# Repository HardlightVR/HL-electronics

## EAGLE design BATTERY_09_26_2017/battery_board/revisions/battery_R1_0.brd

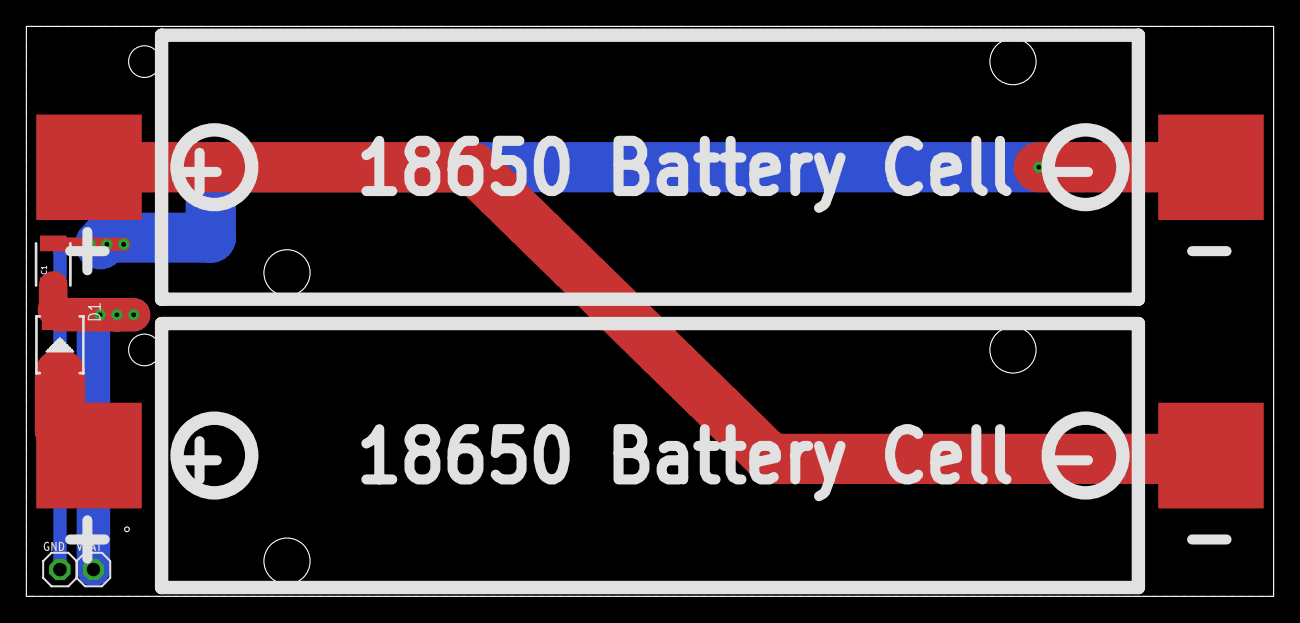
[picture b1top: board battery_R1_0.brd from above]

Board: 2 copper layers, 94.5 x 43.2 mm, 6 parts (0 on the bottom side), 4 nets.

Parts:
C1: 47uF; 1210
CELL1, CELL2: KSE-1042P
D1: 28V-5A; DO-214AA
GND: WPAD-1-PTH-2.54
VBAT: WPAD-1-PTH-2.54

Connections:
7V2: CELL2.+, D1.+
CELL1: CELL1.+, CELL2.-
GND: C1.2, CELL1.-, GND.1
VBAT: C1.1, D1.-, VBAT.1

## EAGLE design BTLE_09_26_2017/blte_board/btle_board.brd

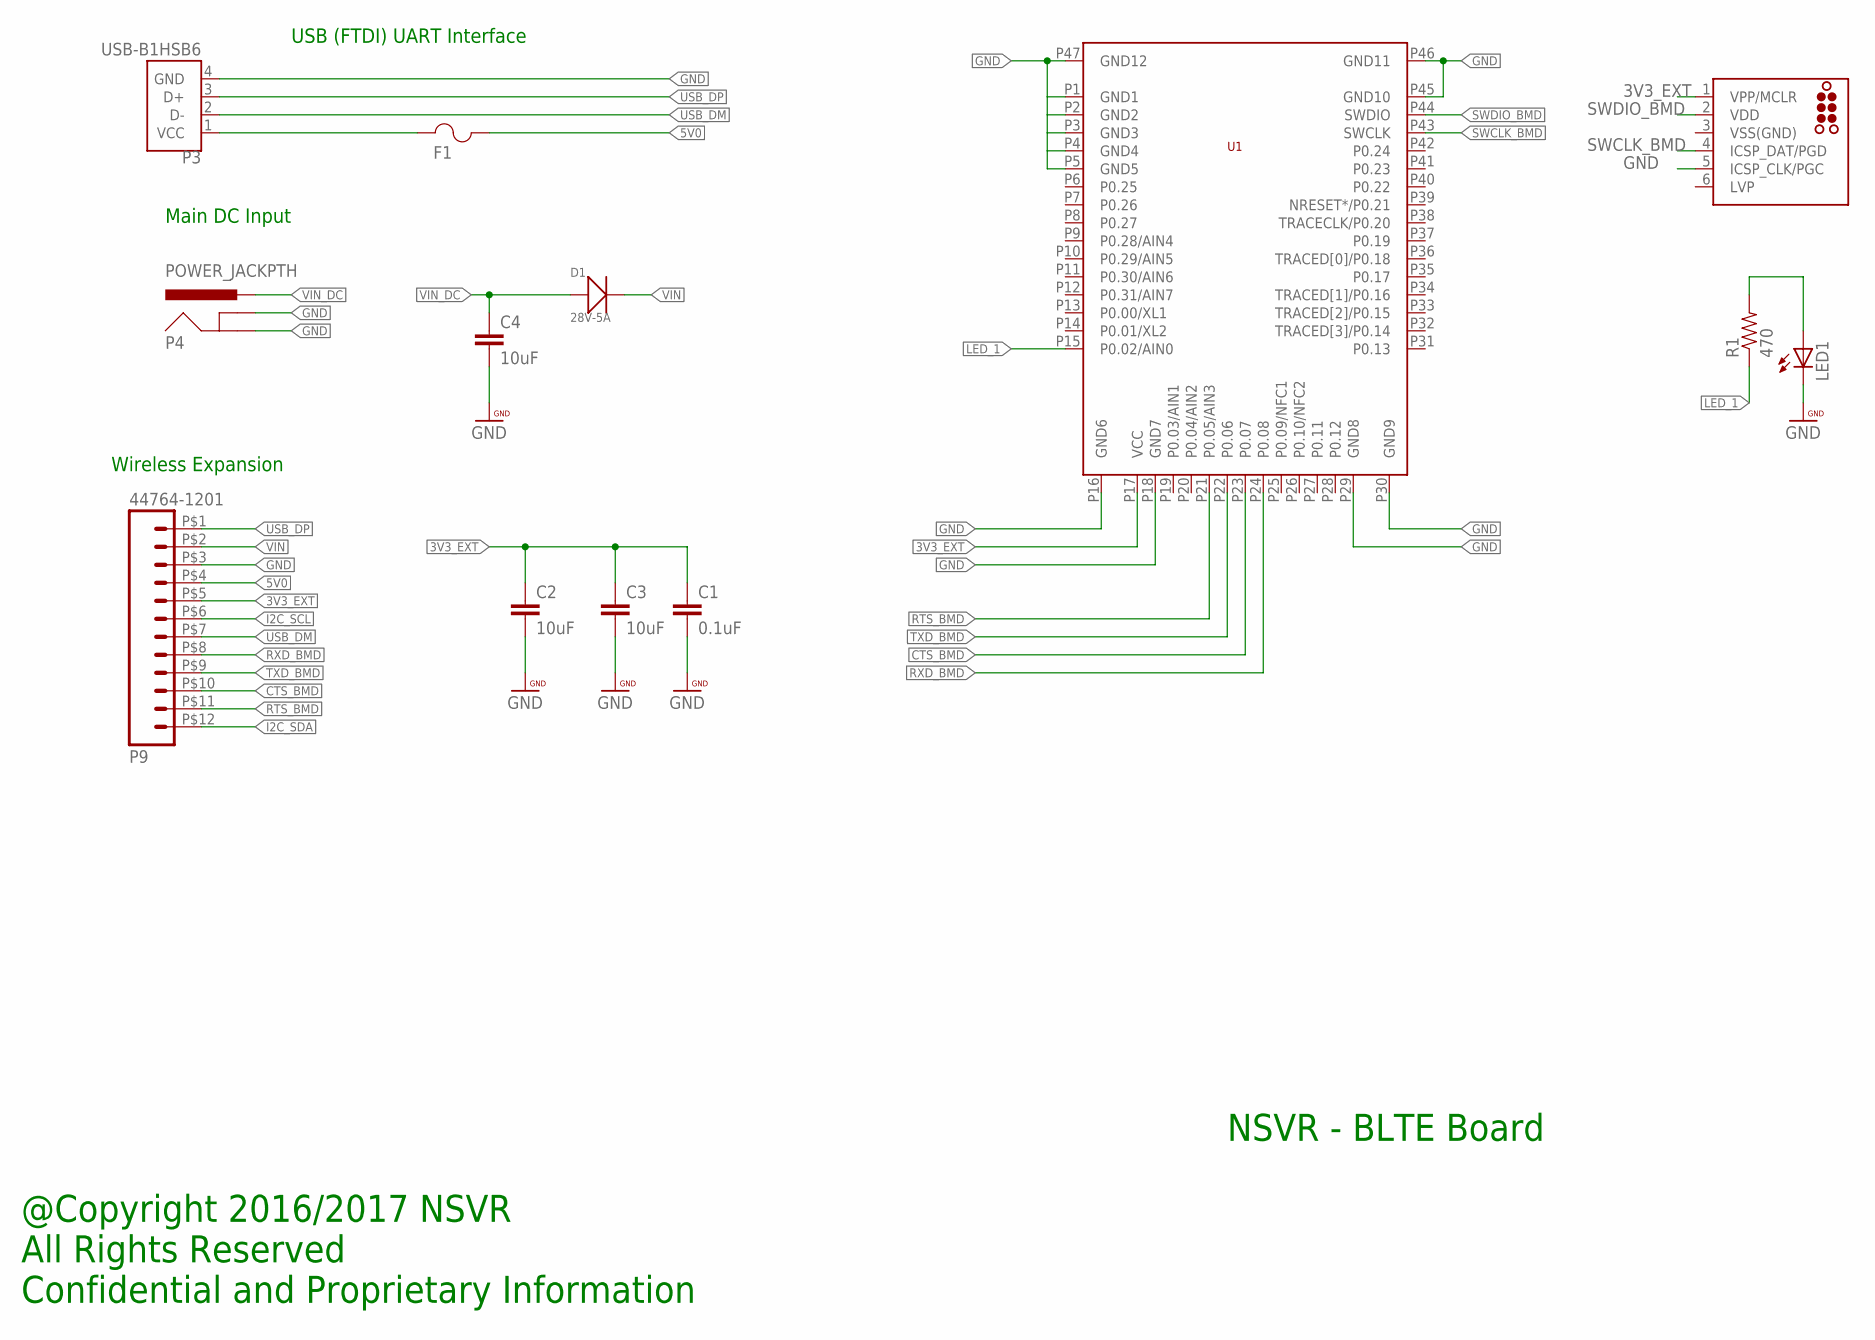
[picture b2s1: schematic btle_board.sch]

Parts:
C1: 0.1uF; 0603-CAP
C2, C3, C4: 10uF; 0603-CAP
D1: 28V-5A; DO-214AA
F1: 1206L050YR; 1206LSERIES
LED1: LEDCHIP-LED0603; CHIP-LED0603
P1: TC2030-MCP-NL
P3: USB-B1HSB6; OST_USB-B1HSB6
P4: POWER_JACKPTH; POWER_JACK_PTH
P9: 44764-1201
R1: 470; EIA-0402
U1: BMD-300

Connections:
3V3_EXT: C1.1, C2.1, C3.1, P1.1 (VPP/MCLR), P9.P$5 (5), U1.P17 (VCC)
5V0: F1.2, P9.P$4 (4)
CTS_BMD: P9.P$10 (10), U1.P23 (P0.07)
GND: C1.2, C2.2, C3.2, C4.2, LED1.C, P1.5 (ICSP_CLK/PGC), P3.4 (GND), P4.GND, P4.GNDBREAK, P9.P$3 (3), U1.P1 (GND1), U1.P2 (GND2), U1.P3 (GND3), U1.P4 (GND4), U1.P5 (GND5), U1.P16 (GND6), U1.P18 (GND7), U1.P29 (GND8), U1.P30 (GND9), U1.P45 (GND10), U1.P46 (GND11), U1.P47 (GND12)
I2C_SCL: P9.P$6 (6)
I2C_SDA: P9.P$12 (12)
LED1: LED1.A, R1.2
LED_1: R1.1, U1.P15 (P0.02/AIN0)
RTS_BMD: P9.P$11 (11), U1.P21 (P0.05/AIN3)
RXD_BMD: P9.P$8 (8), U1.P24 (P0.08)
SWCLK_BMD: P1.4 (ICSP_DAT/PGD), U1.P43 (SWCLK)
SWDIO_BMD: P1.2 (VDD), U1.P44 (SWDIO)
TXD_BMD: P9.P$9 (9), U1.P22 (P0.06)
USB_DM: P3.2 (D-), P9.P$7 (7)
USB_DP: P3.3 (D+), P9.P$1 (1)
VBUS_IN: F1.1, P3.1 (VCC)
VIN: D1.-, P9.P$2 (2)
VIN_DC: C4.1, D1.+, P4.PWR
VSS(GND): P1.3 (VSS(GND))

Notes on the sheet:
Wireless Expansion
Main DC Input
USB (FTDI) UART Interface
@Copyright 2016/2017 NSVR All Rights Reserved Confidential and Proprietary Information
NSVR - BLTE Board

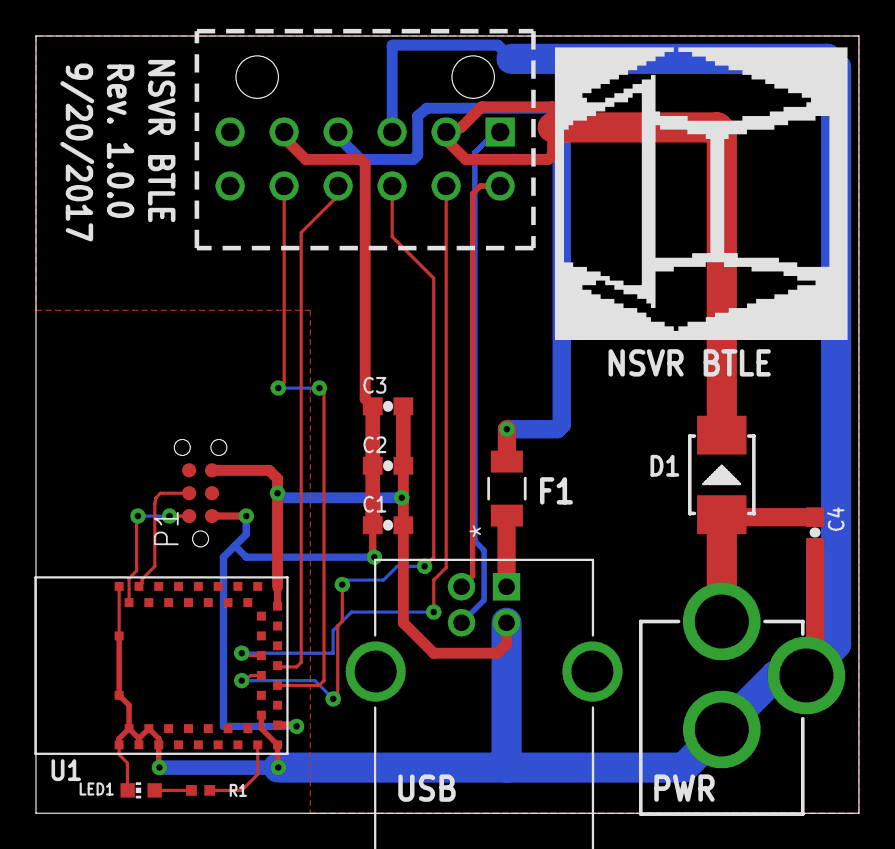
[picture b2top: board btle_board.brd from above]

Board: 2 copper layers, 45.7 x 43.2 mm, 15 parts (1 on the bottom side), 16 nets.

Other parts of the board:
U$4, U$5: NSVR_LOGO

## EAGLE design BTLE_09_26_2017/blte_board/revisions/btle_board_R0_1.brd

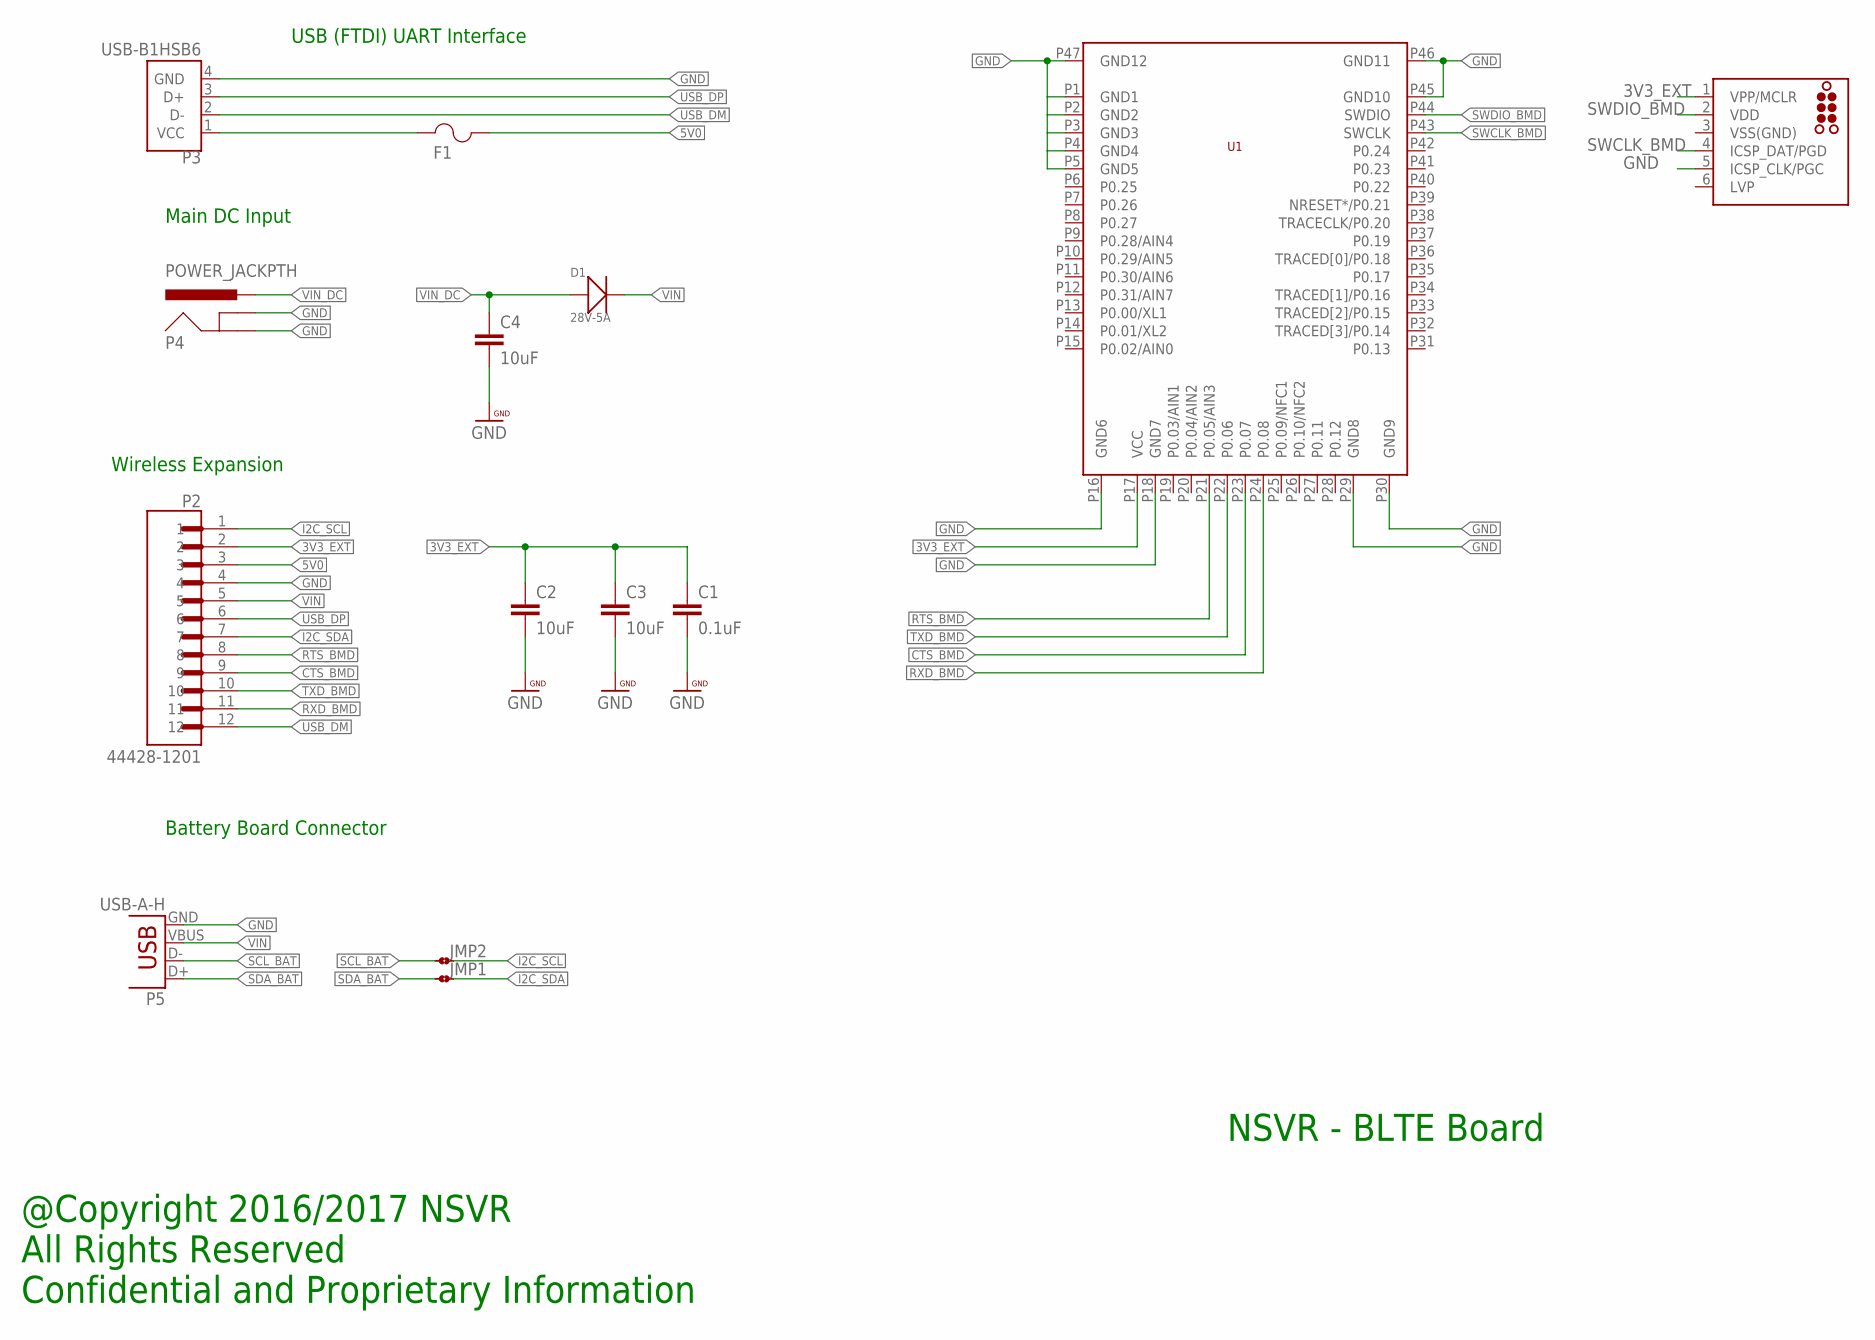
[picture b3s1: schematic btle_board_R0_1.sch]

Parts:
C1: 0.1uF; 0603-CAP
C2, C3, C4: 10uF; 0603-CAP
D1: 28V-5A; DO-214AA
F1: 1206L050YR; 1206LSERIES
JMP1, JMP2: JMP-2-NO-0402
P1: TC2030-MCP-NL
P2: 44428-1201; MOLEX_44428-1201
P3: USB-B1HSB6; OST_USB-B1HSB6
P4: POWER_JACKPTH; POWER_JACK_PTH
P5: USB-A-H
U1: BMD-300

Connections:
3V3_EXT: C1.1, C2.1, C3.1, P1.1 (VPP/MCLR), P2.2, U1.P17 (VCC)
5V0: F1.2, P2.3
CTS_BMD: P2.9, U1.P23 (P0.07)
GND: C1.2, C2.2, C3.2, C4.2, P1.5 (ICSP_CLK/PGC), P2.4, P3.4 (GND), P4.GND, P4.GNDBREAK, P5.GND, U1.P1 (GND1), U1.P2 (GND2), U1.P3 (GND3), U1.P4 (GND4), U1.P5 (GND5), U1.P16 (GND6), U1.P18 (GND7), U1.P29 (GND8), U1.P30 (GND9), U1.P45 (GND10), U1.P46 (GND11), U1.P47 (GND12)
I2C_SCL: JMP2.2, P2.1
I2C_SDA: JMP1.2, P2.7
RTS_BMD: P2.8, U1.P21 (P0.05/AIN3)
RXD_BMD: P2.11, U1.P24 (P0.08)
SCL_BAT: JMP2.1, P5.D-
SDA_BAT: JMP1.1, P5.D+
SWCLK_BMD: P1.4 (ICSP_DAT/PGD), U1.P43 (SWCLK)
SWDIO_BMD: P1.2 (VDD), U1.P44 (SWDIO)
TXD_BMD: P2.10, U1.P22 (P0.06)
USB_DM: P2.12, P3.2 (D-)
USB_DP: P2.6, P3.3 (D+)
VBUS_IN: F1.1, P3.1 (VCC)
VIN: D1.-, P2.5, P5.VBUS
VIN_DC: C4.1, D1.+, P4.PWR
VSS(GND): P1.3 (VSS(GND))

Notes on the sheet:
Wireless Expansion
Main DC Input
USB (FTDI) UART Interface
Battery Board Connector
@Copyright 2016/2017 NSVR All Rights Reserved Confidential and Proprietary Information
NSVR - BLTE Board

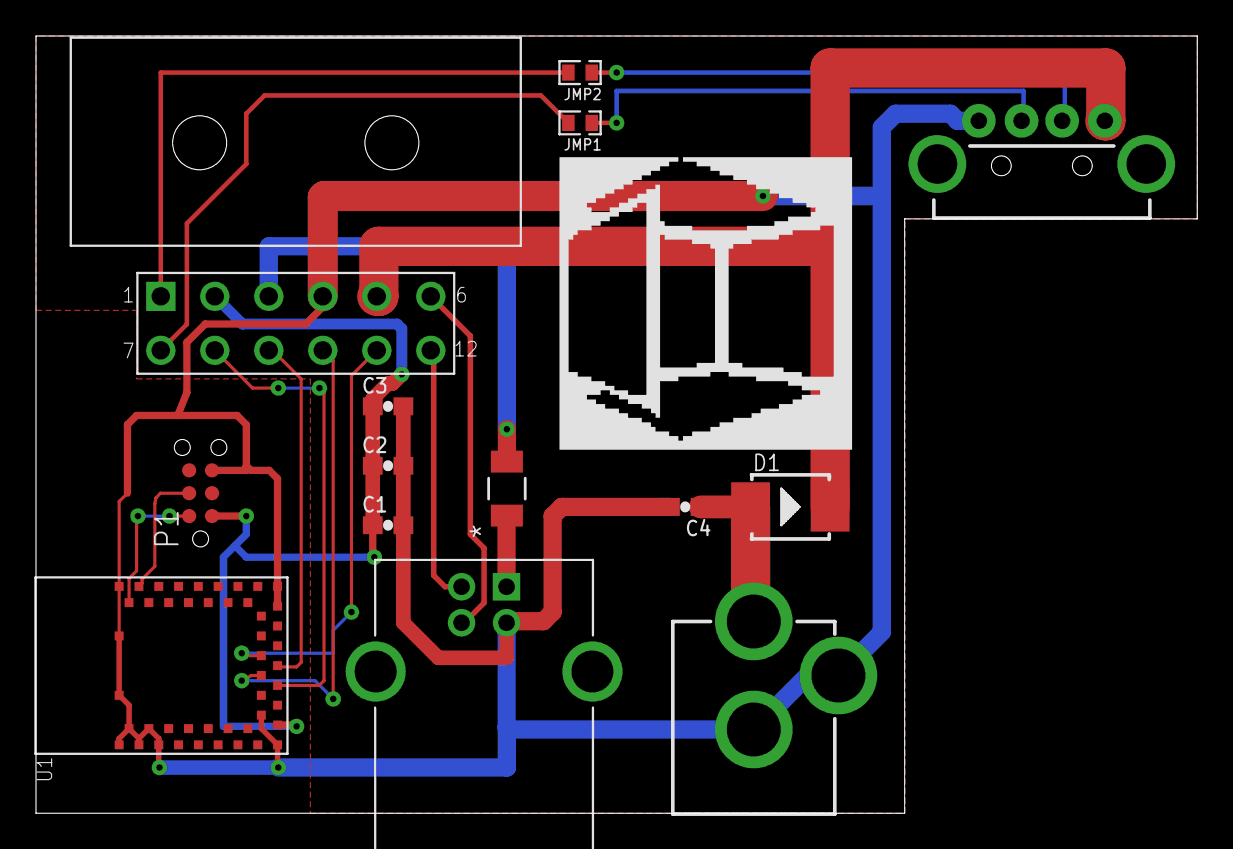
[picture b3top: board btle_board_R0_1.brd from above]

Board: 2 copper layers, 64.5 x 43.2 mm, 16 parts (1 on the bottom side), 18 nets.

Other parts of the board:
U$4, U$100: NSVR_LOGO

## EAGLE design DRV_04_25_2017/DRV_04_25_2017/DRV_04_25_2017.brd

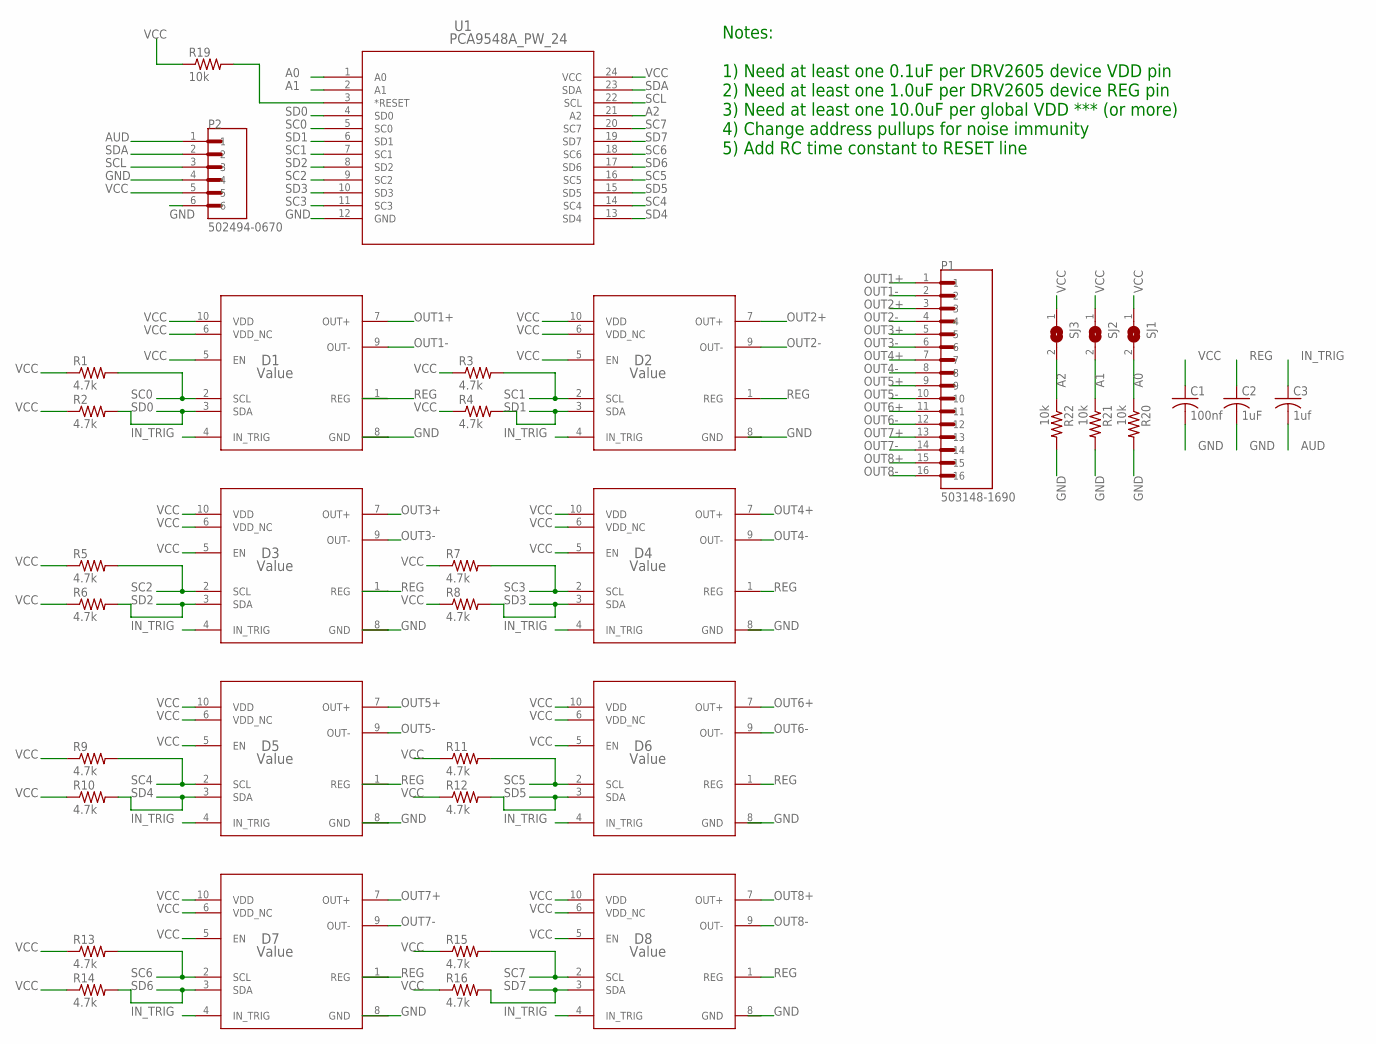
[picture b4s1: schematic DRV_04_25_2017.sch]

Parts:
C1: 100nf; C0603
C2: 1uF; C0603
C3: 1uf; C0603
D1, D2, D3, D4, D5, D6, D7, D8: Value; DGS0010A
P1: 503148-1690; MOLEX_503148-1690
P2: 502494-0670; MOLEX_502494-0670
R1, R2, R3, R4, R5, R6, R7, R8, R9, R10, R11, R12, R13, R14, R15, R16: 4.7k; R0402
R19, R20, R21, R22: 10k; R0402
SJ1, SJ2, SJ3: SJ
U1: PCA9548A_PW_24; PW24

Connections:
A0: R20.1, SJ1.2, U1.1 (A0)
A1: R21.1, SJ2.2, U1.2 (A1)
A2: R22.1, SJ3.2, U1.21 (A2)
AUD: C3.2, P2.1
GND: C1.2, C2.2, D1.8 (GND), D2.8 (GND), D3.8 (GND), D4.8 (GND), D5.8 (GND), D6.8 (GND), D7.8 (GND), D8.8 (GND), P2.4, P2.6, R20.2, R21.2, R22.2, U1.12 (GND)
IN_TRIG: C3.1, D1.4 (IN_TRIG), D2.4 (IN_TRIG), D3.4 (IN_TRIG), D4.4 (IN_TRIG), D5.4 (IN_TRIG), D6.4 (IN_TRIG), D7.4 (IN_TRIG), D8.4 (IN_TRIG)
OUT1+: D1.7 (OUT+), P1.1
OUT1-: D1.9 (OUT-), P1.2
OUT2+: D2.7 (OUT+), P1.3
OUT2-: D2.9 (OUT-), P1.4
OUT3+: D3.7 (OUT+), P1.5
OUT3-: D3.9 (OUT-), P1.6
OUT4+: D4.7 (OUT+), P1.7
OUT4-: D4.9 (OUT-), P1.8
OUT5+: D5.7 (OUT+), P1.9
OUT5-: D5.9 (OUT-), P1.10
OUT6+: D6.7 (OUT+), P1.11
OUT6-: D6.9 (OUT-), P1.12
OUT7+: D7.7 (OUT+), P1.13
OUT7-: D7.9 (OUT-), P1.14
OUT8+: D8.7 (OUT+), P1.15
OUT8-: D8.9 (OUT-), P1.16
REG: C2.1, D1.1 (REG), D2.1 (REG), D3.1 (REG), D4.1 (REG), D5.1 (REG), D6.1 (REG), D7.1 (REG), D8.1 (REG)
RESET: R19.2, U1.3 (*RESET)
SC0: D1.2 (SCL), R1.2, U1.5 (SC0)
SC1: D2.2 (SCL), R3.2, U1.7 (SC1)
SC2: D3.2 (SCL), R5.2, U1.9 (SC2)
SC3: D4.2 (SCL), R7.2, U1.11 (SC3)
SC4: D5.2 (SCL), R9.2, U1.14 (SC4)
SC5: D6.2 (SCL), R11.2, U1.16 (SC5)
SC6: D7.2 (SCL), R13.2, U1.18 (SC6)
SC7: D8.2 (SCL), R15.2, U1.20 (SC7)
SCL: P2.3, U1.22 (SCL)
SD0: D1.3 (SDA), R2.2, U1.4 (SD0)
SD1: D2.3 (SDA), R4.2, U1.6 (SD1)
SD2: D3.3 (SDA), R6.2, U1.8 (SD2)
SD3: D4.3 (SDA), R8.2, U1.10 (SD3)
SD4: D5.3 (SDA), R10.2, U1.13 (SD4)
SD5: D6.3 (SDA), R12.2, U1.15 (SD5)
SD6: D7.3 (SDA), R14.2, U1.17 (SD6)
SD7: D8.3 (SDA), R16.2, U1.19 (SD7)
SDA: P2.2, U1.23 (SDA)
VCC: C1.1, D1.5 (EN), D1.6 (VDD_NC), D1.10 (VDD), D2.5 (EN), D2.6 (VDD_NC), D2.10 (VDD), D3.5 (EN), D3.6 (VDD_NC), D3.10 (VDD), D4.5 (EN), D4.6 (VDD_NC), D4.10 (VDD), D5.5 (EN), D5.6 (VDD_NC), D5.10 (VDD), D6.5 (EN), D6.6 (VDD_NC), D6.10 (VDD), D7.5 (EN), D7.6 (VDD_NC), D7.10 (VDD), D8.5 (EN), D8.6 (VDD_NC), D8.10 (VDD), P2.5, R1.1, R2.1, R3.1, R4.1, R5.1, R6.1, R7.1, R8.1, R9.1, R10.1, R11.1, R12.1, R13.1, R14.1, R15.1, R16.1, R19.1, SJ1.1, SJ2.1, SJ3.1, U1.24 (VCC)

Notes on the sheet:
Notes: 1) Need at least one 0.1uF per DRV2605 device VDD pin 2) Need at least one 1.0uF per DRV2605 device REG pin 3) Need at least one 10.0uF per global VDD *** (or more) 4) Change address pullups for noise immunity 5) Add RC time constant to RESET line

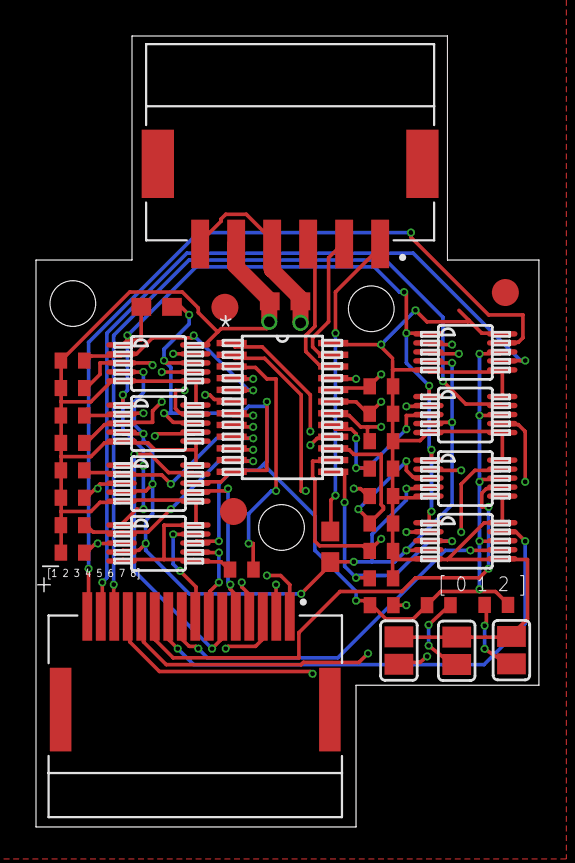
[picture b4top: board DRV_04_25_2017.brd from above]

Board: 4 copper layers, 27.9 x 43.9 mm, 40 parts (0 on the bottom side), 43 nets.

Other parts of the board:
U$1, U$2, U$4: FIDUCIAL_G15

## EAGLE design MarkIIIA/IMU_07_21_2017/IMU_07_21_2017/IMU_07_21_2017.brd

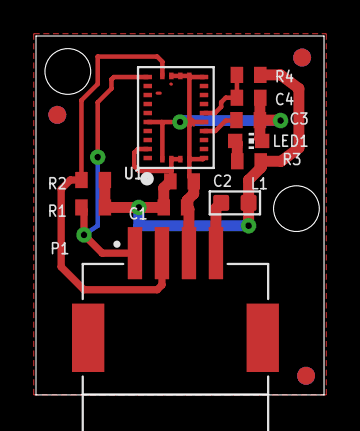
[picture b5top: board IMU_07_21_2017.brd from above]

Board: 2 copper layers, 16.0 x 19.9 mm, 15 parts (0 on the bottom side), 8 nets.

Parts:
$$U$2: CIRCLE-1MM-2R
C1: 10uF; C0402
C2, C3, C4: 0.1u; C0402
L1: 120OHM-500MA; L0603
LED1: CHIP-LED0603
P1: 502585-0470; MOLEX_502585-0470
R1, R2, R4: 4.7k; R0402
R3: 220; R0402
U1: BNO055
U$1, U$3: CIRCLE-1MM-2R

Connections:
3V3_EXT: L1.2, P1.4
!RST: C4.1, R4.2, U1.11
CAP: C3.1, U1.9
GND: C1.2, C2.2, C3.2, C4.2, LED1.C, P1.3, U1.2, U1.5, U1.6, U1.10, U1.15, U1.16, U1.17, U1.18, U1.25
unnamed: LED1.A, R3.2
SCL: P1.2, R2.2, U1.19
SDA: P1.1, R1.2, U1.20
VDD: C1.1, C2.1, L1.1, R1.1, R2.1, R3.1, R4.1, U1.3, U1.4, U1.28

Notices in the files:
parts and their libraries:
PatternAgents-ProtoPads: License : http://creativecommons.org/licenses/by-sa/4.0
(Creative Commons 4.0)
tag-connect: ©2009 ROFA.cz - modified and updated by Robert Darlington ‹rdarlington@gmail.com›
COPYRIGHT: Copyright C 2015 Accelerated Designs. All rights reserved
